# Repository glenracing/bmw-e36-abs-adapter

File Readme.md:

# bmw-e36-abs-adapter

BMW E36 ABS pedal travel sensor adapter and CANbus module.

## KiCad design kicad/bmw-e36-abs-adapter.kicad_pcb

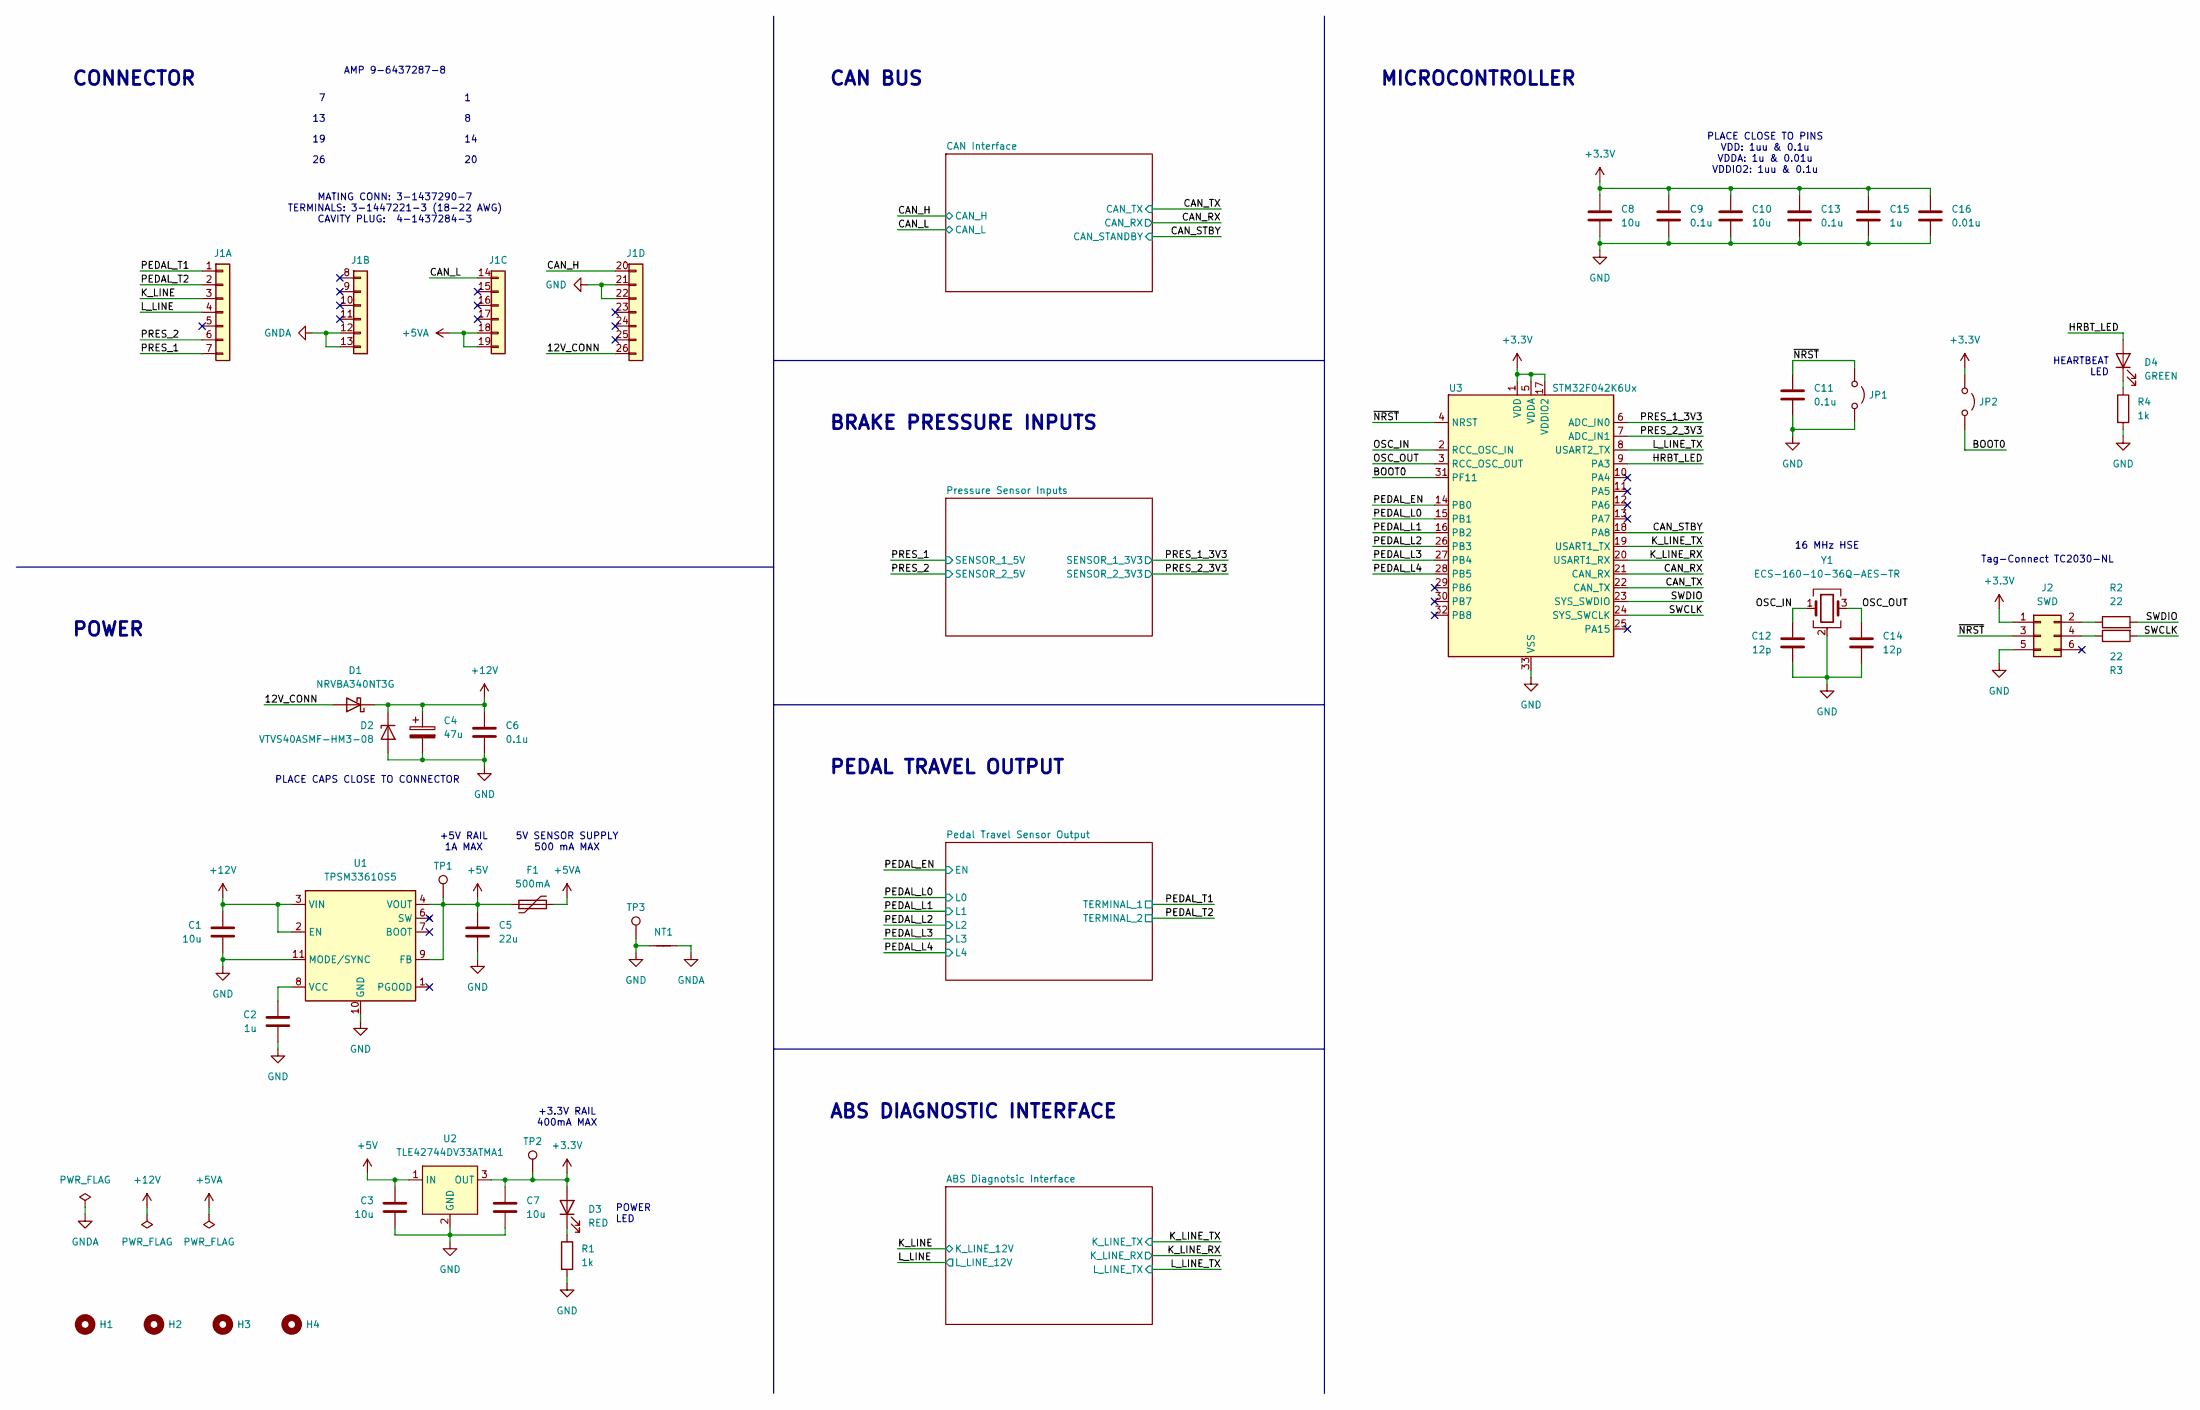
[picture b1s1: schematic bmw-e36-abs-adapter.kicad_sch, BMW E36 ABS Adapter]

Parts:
C1, C3, C7, C8, C10: 10u; C_1206_3216Metric; Part Number GRT31CR61H106KE01L
C2, C15: 1u; C_0603_1608Metric; Part Number GRT188R71E105KE13D
C4: 47u; CP_Elec_8x6.5; Part Number UCD1H470MCL6GS
C5: 22u; C_1206_3216Metric; Part Number GRT31CC81C226KE01L
C6, C9, C11, C13: 0.1u; C_0603_1608Metric; Part Number GCJ188R71H104KA12D
C12, C14: 12p; C_0603_1608Metric; Part Number GCM1885C2A120JA16D
C16: 0.01u; C_0603_1608Metric; Part Number GCM188R71H103KA37D
D1: NRVBA340NT3G; D_SMA; Part Number NRVBA340NT3G
D2: VTVS40ASMF-HM3-08; D_SMF; Part Number VTVS40ASMF-HM3-08
D3: RED; LED_0603_1608Metric; Part Number SML-D12V8WT86C
D4: GREEN; LED_0603_1608Metric; Part Number SML-D12P8WT86C
F1: 500mA; Fuse_1206_3216Metric; Part Number 0ZCJ0050AF2E
H1, H2, H3, H4: MountingHole; MountingHole_3.2mm_M3
J1: TE_9-6437287-8; Part Number 9-6437287-8
J2: SWD; Tag-Connect_TC2030-IDC-NL_2x03_P1.27mm_Vertical
JP1: RST; SolderJumper-2_P1.3mm_Open_RoundedPad1.0x1.5mm
JP2: BOOT; SolderJumper-2_P1.3mm_Open_RoundedPad1.0x1.5mm
NT1: NetTie_2; NetTie-2_SMD_Pad0.5mm
R1, R4: 1k; R_0603_1608Metric; Part Number ERJ-3EKF1001V
R2, R3: 22; R_0603_1608Metric; Part Number ERJ-3EKF22R0V
TP1, TP2: TestPoint; TestPoint_Pad_D1.5mm
TP3: TestPoint; TestPoint_Keystone_5000-5004_Miniature
U1: TPSM33610S5; Texas_RDN0011B_QFN-FCMOD-11-3.5x4.5mm-P0.5mm_2EP; Part Number TPSM33610S5QRDNRQ1
U2: TLE42744DV33ATMA1; TO-252-2; Part Number TLE42744DV33ATMA1
U3: STM32F042K6Ux; QFN-32-1EP_5x5mm_P0.5mm_EP3.45x3.45mm; Part Number STM32F042K6U6
Y1: ECS-160-10-36Q-AES-TR; Crystal_SMD_2520-4Pin_2.5x2.0mm; Part Number ECS-160-10-36Q-AES-TR

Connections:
+5VA: F1.2, J1.18, J1.19
+12V: C1.1, C4.1, C6.1, D1.1 (K), D2.1 (K), U1.2 (EN), U1.3 (VIN); also elsewhere on the board
/12V_CONN: D1.2 (A), J1.26
/BOOT0: JP2.2 (B), U3.31 (PF11)
/CAN_H: J1.20; also elsewhere on the board
/CAN_L: J1.14; also elsewhere on the board
/CAN_RX: U3.21 (CAN_RX); also elsewhere on the board
/CAN_STBY: U3.18 (PA8); also elsewhere on the board
/CAN_TX: U3.22 (CAN_TX); also elsewhere on the board
/HRBT_LED: D4.2 (A), U3.9 (PA3)
/K_LINE: J1.3; also elsewhere on the board
/K_LINE_RX: U3.20 (USART1_RX); also elsewhere on the board
/K_LINE_TX: U3.19 (USART1_TX); also elsewhere on the board
/L_LINE: J1.4; also elsewhere on the board
/L_LINE_TX: U3.8 (USART2_TX); also elsewhere on the board
/OSC_IN: C12.1, U3.2 (RCC_OSC_IN), Y1.1
/OSC_OUT: C14.1, U3.3 (RCC_OSC_OUT), Y1.3
/PEDAL_EN: U3.14 (PB0); also elsewhere on the board
/PEDAL_L0: U3.15 (PB1); also elsewhere on the board
/PEDAL_L1: U3.16 (PB2); also elsewhere on the board
/PEDAL_L2: U3.26 (PB3); also elsewhere on the board
/PEDAL_L3: U3.27 (PB4); also elsewhere on the board
/PEDAL_L4: U3.28 (PB5); also elsewhere on the board
/PEDAL_T1: J1.1; also elsewhere on the board
/PEDAL_T2: J1.2; also elsewhere on the board
/PRES_1: J1.7; also elsewhere on the board
/PRES_1_3V3: U3.6 (ADC_IN0); also elsewhere on the board
/PRES_2: J1.6; also elsewhere on the board
/PRES_2_3V3: U3.7 (ADC_IN1); also elsewhere on the board
/SWCLK: R3.2, U3.24 (SYS_SWCLK)
/SWDIO: R2.2, U3.23 (SYS_SWDIO)
/~NRST: C11.1, J2.3, JP1.1 (A), U3.4 (NRST)
GNDA: J1.12, J1.13, NT1.2; also elsewhere on the board
unnamed: D3.1 (K), R1.1
unnamed: D4.1 (K), R4.1
unnamed: J2.2, R2.1
unnamed: J2.4, R3.1
unnamed: C2.1, U1.8 (VCC)

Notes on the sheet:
16 MHz HSE
HEARTBEAT LED
PEDAL TRAVEL OUTPUT
AMP 9-6437287-8
Tag-Connect TC2030-NL
+5V RAIL 1A MAX
POWER LED
CONNECTOR
CAN BUS
PLACE CLOSE TO PINS VDD: 1uu & 0.1u VDDA: 1u & 0.01u VDDIO2: 1uu & 0.1u
MATING CONN: 3-1437290-7 TERMINALS: 3-1447221-3 (18-22 AWG) CAVITY PLUG: 4-1437284-3
MICROCONTROLLER
BRAKE PRESSURE INPUTS
+3.3V RAIL 400mA MAX
5V SENSOR SUPPLY 500 mA MAX
PLACE CAPS CLOSE TO CONNECTOR
ABS DIAGNOSTIC INTERFACE
POWER

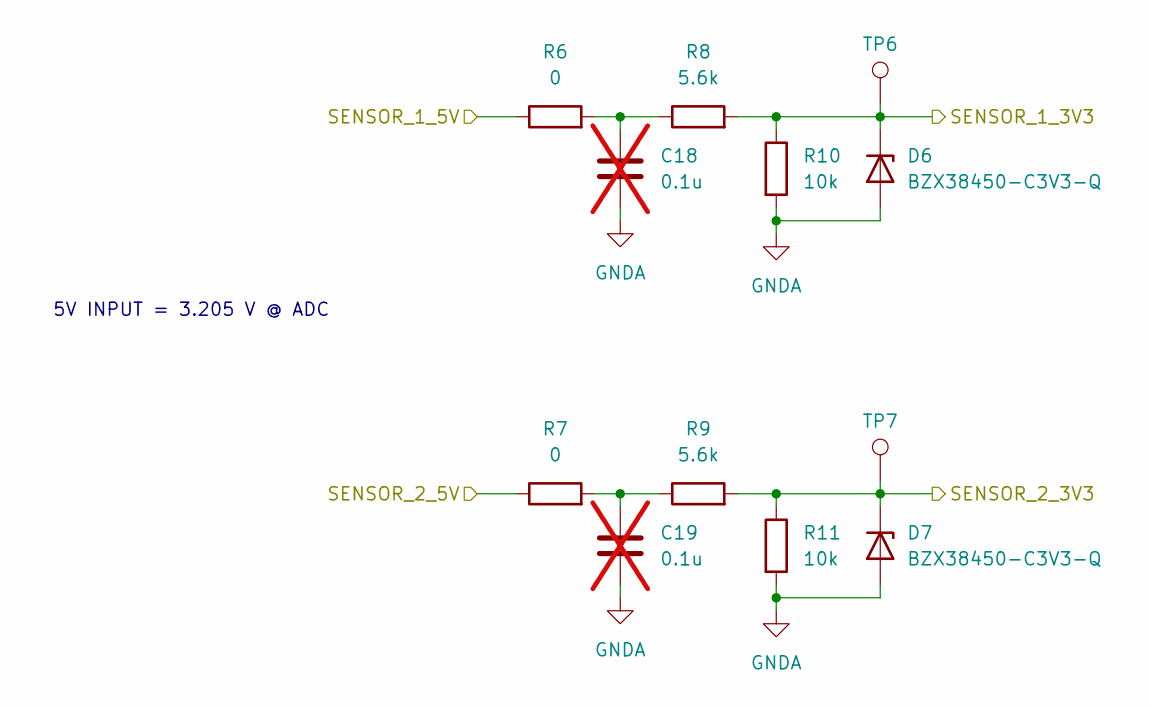
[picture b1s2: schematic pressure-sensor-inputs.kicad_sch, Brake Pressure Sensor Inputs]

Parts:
C18, C19: 0.1u; C_0603_1608Metric; Part Number GCJ188R71H104KA12D; not fitted
D6, D7: BZX38450-C3V3-Q; D_SOD-323; Part Number BZX38450-C3V3-Q
R6, R7: 0; R_0603_1608Metric; Part Number ERJ-H3G0R00V
R8, R9: 5.6k; R_0603_1608Metric; Part Number ERJ-3EKF5601V
R10, R11: 10k; R_0603_1608Metric; Part Number ERJ-3EKF1002V
TP6, TP7: TestPoint; TestPoint_Pad_D1.5mm

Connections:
/PRES_1: R6.1; also elsewhere on the board
/PRES_1_3V3: D6.1 (K), R8.2, R10.1, TP6.1 (1_1); also elsewhere on the board
/PRES_2: R7.1; also elsewhere on the board
/PRES_2_3V3: D7.1 (K), R9.2, R11.1, TP7.1 (1_1); also elsewhere on the board
GNDA: C18.2, C19.2, D6.2 (A), D7.2 (A), R10.2, R11.2; also elsewhere on the board
unnamed: C18.1, R6.2, R8.1
unnamed: C19.1, R7.2, R9.1

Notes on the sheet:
5V INPUT = 3.205 V @ ADC

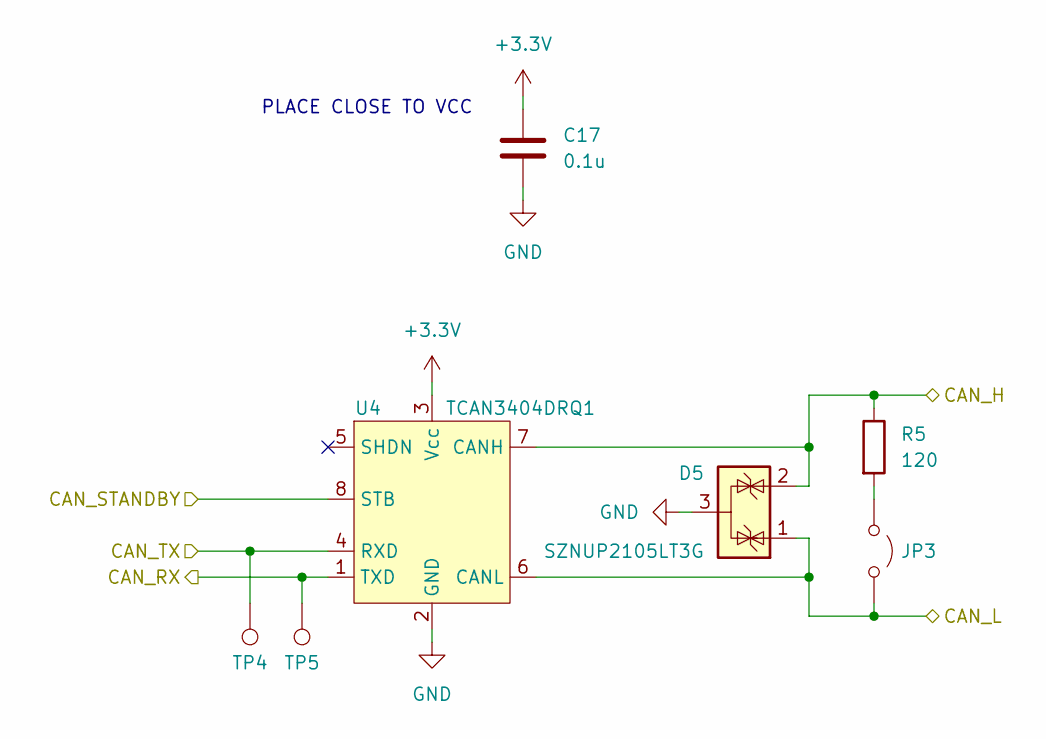
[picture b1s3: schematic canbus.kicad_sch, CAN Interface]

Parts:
C17: 0.1u; C_0603_1608Metric; Part Number GCJ188R71H104KA12D
D5: SZNUP2105LT3G; SOT-23; Part Number SZNUP2105LT3G
JP3: TERM; PinHeader_1x02_P2.54mm_Vertical; Part Number 61300211121
R5: 120; R_0603_1608Metric; Part Number ERJ-3EKF1200V
TP4, TP5: TestPoint; TestPoint_Pad_D1.5mm
U4: TCAN3404DRQ1; JEITA_SOIC-8_3.9x4.9mm_P1.27mm; Part Number TCAN3404DRQ1

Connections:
/CAN_H: D5.2 (K), R5.1, U4.7 (CANH); also elsewhere on the board
/CAN_L: D5.1 (K), JP3.2 (B), U4.6 (CANL); also elsewhere on the board
/CAN_RX: TP5.1 (1_1), U4.1 (TXD); also elsewhere on the board
/CAN_STBY: U4.8 (STB); also elsewhere on the board
/CAN_TX: TP4.1 (1_1), U4.4 (RXD); also elsewhere on the board
unnamed: JP3.1 (A), R5.2

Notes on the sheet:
PLACE CLOSE TO VCC

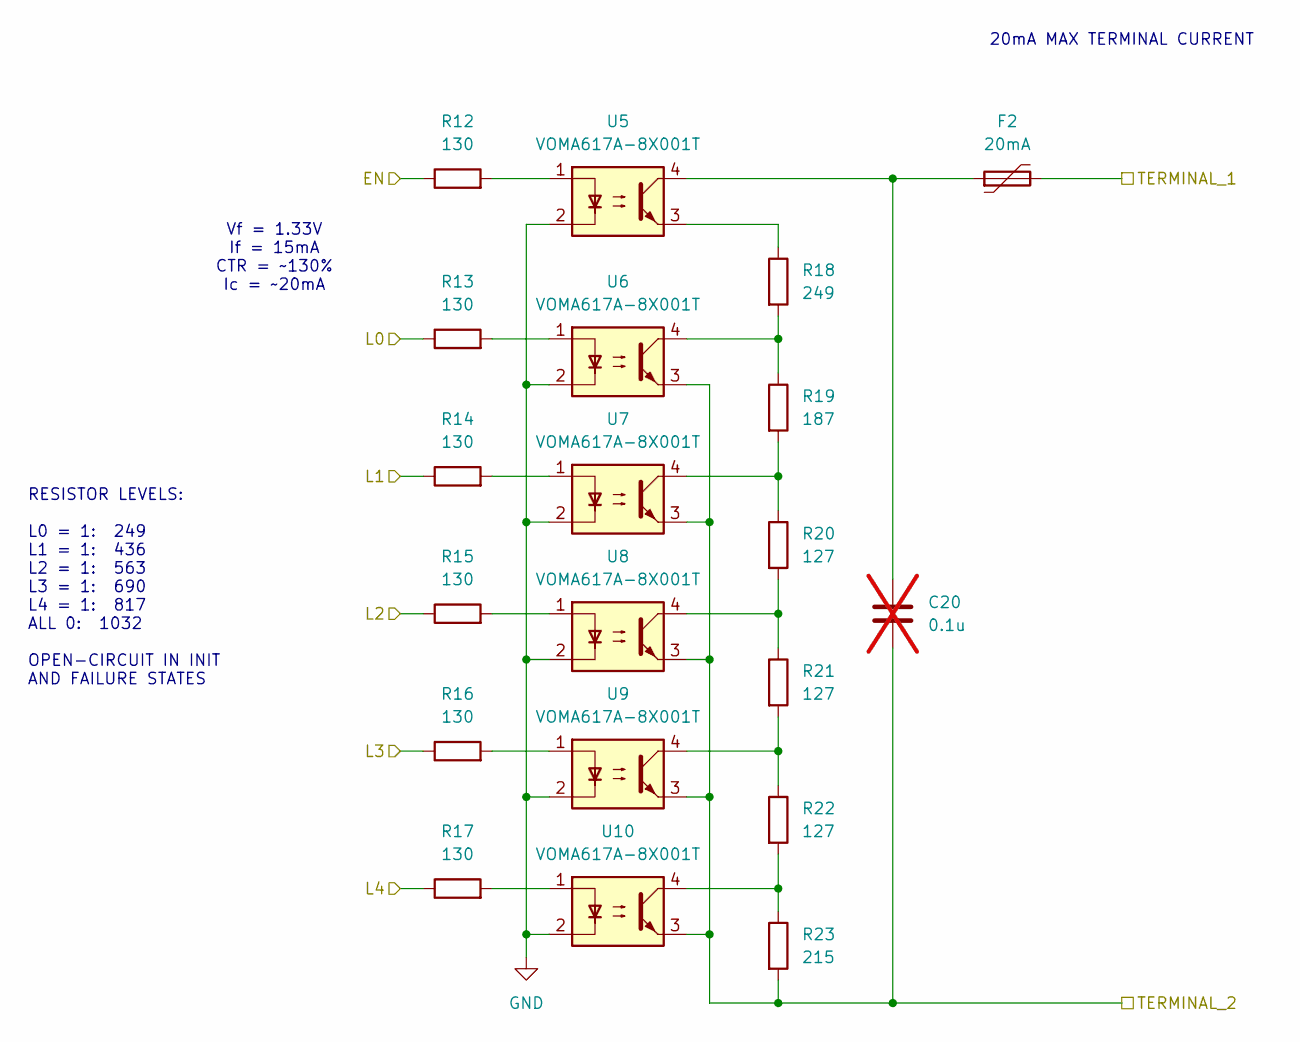
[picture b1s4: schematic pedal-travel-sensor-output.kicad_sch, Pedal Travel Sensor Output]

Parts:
C20: 0.1u; C_0603_1608Metric; Part Number GCJ188R71H104KA12D; not fitted
F2: 20mA; Fuse_0603_1608Metric; Part Number 0ZCM0002FF2G
R12, R13, R14, R15, R16, R17: 130; R_0603_1608Metric; Part Number ERJ-3EKF1300V
R18: 249; R_0603_1608Metric; Part Number ERJ-3EKF2490V
R19: 187; R_0603_1608Metric; Part Number ERJ-3EKF1870V
R20, R21, R22: 127; R_0603_1608Metric; Part Number ERJ-3EKF1270V
R23: 215; R_0603_1608Metric; Part Number ERJ-3EKF2150V
U5, U6, U7, U8, U9, U10: VOMA617A-8X001T; SOP-4_4.4x4.6mm_P2.54mm; Part Number VOMA617A-8X001T

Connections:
/PEDAL_EN: R12.1; also elsewhere on the board
/PEDAL_L0: R13.1; also elsewhere on the board
/PEDAL_L1: R14.1; also elsewhere on the board
/PEDAL_L2: R15.1; also elsewhere on the board
/PEDAL_L3: R16.1; also elsewhere on the board
/PEDAL_L4: R17.1; also elsewhere on the board
/PEDAL_T1: F2.2; also elsewhere on the board
/PEDAL_T2: C20.2, R23.2, U6.3, U7.3, U8.3, U9.3, U10.3; also elsewhere on the board
unnamed: C20.1, F2.1, U5.4
unnamed: R12.2, U5.1
unnamed: R13.2, U6.1
unnamed: R14.2, U7.1
unnamed: R15.2, U8.1
unnamed: R16.2, U9.1
unnamed: R17.2, U10.1
unnamed: R18.1, U5.3
unnamed: R18.2, R19.1, U6.4
unnamed: R19.2, R20.1, U7.4
unnamed: R20.2, R21.1, U8.4
unnamed: R21.2, R22.1, U9.4
unnamed: R22.2, R23.1, U10.4

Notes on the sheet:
20mA MAX TERMINAL CURRENT
Vf = 1.33V If = 15mA CTR = ~130% Ic = ~20mA
RESISTOR LEVELS: L0 = 1: 249 L1 = 1: 436 L2 = 1: 563 L3 = 1: 690 L4 = 1: 817 ALL 0: 1032 OPEN-CIRCUIT IN INIT AND FAILURE STATES

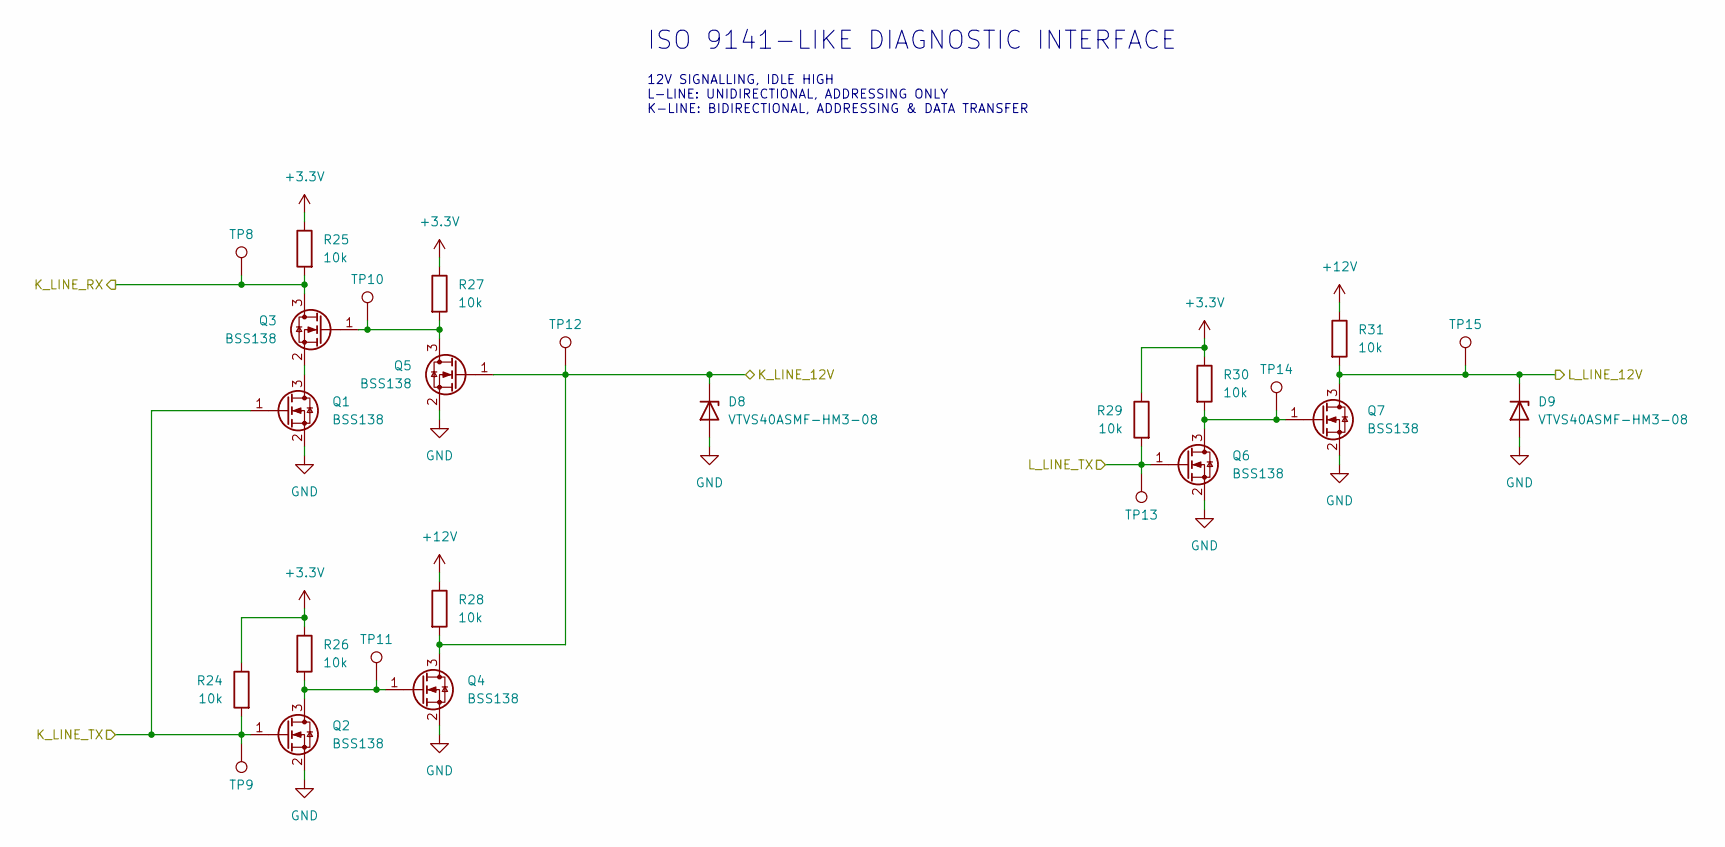
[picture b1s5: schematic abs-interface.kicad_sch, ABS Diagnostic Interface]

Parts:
D8, D9: VTVS40ASMF-HM3-08; D_SMF; Part Number VTVS40ASMF-HM3-08
Q1, Q2, Q3, Q4, Q5, Q6, Q7: BSS138; SOT-323_SC-70; Part Number BSS138PW,115
R24, R25, R26, R27, R28, R29, R30, R31: 10k; R_0603_1608Metric; Part Number ERJ-3EKF1002V
TP8, TP9, TP10, TP11, TP12, TP13, TP14, TP15: TestPoint; TestPoint_Pad_D1.5mm

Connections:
+12V: R28.1, R31.1; also elsewhere on the board
/K_LINE: D8.1 (K), Q4.3 (D), Q5.1 (G), R28.2, TP12.1 (1_1); also elsewhere on the board
/K_LINE_RX: Q3.3 (D), R25.2, TP8.1 (1_1); also elsewhere on the board
/K_LINE_TX: Q1.1 (G), Q2.1 (G), R24.2, TP9.1 (1_1); also elsewhere on the board
/L_LINE: D9.1 (K), Q7.3 (D), R31.2, TP15.1 (1_1); also elsewhere on the board
/L_LINE_TX: Q6.1 (G), R29.2, TP13.1 (1_1); also elsewhere on the board
unnamed: Q1.3 (D), Q3.2 (S)
unnamed: Q2.3 (D), Q4.1 (G), R26.2, TP11.1 (1_1)
unnamed: Q3.1 (G), Q5.3 (D), R27.2, TP10.1 (1_1)
unnamed: Q6.3 (D), Q7.1 (G), R30.2, TP14.1 (1_1)

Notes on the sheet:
ISO 9141-LIKE DIAGNOSTIC INTERFACE
12V SIGNALLING, IDLE HIGH L-LINE: UNIDIRECTIONAL, ADDRESSING ONLY K-LINE: BIDIRECTIONAL, ADDRESSING & DATA TRANSFER

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
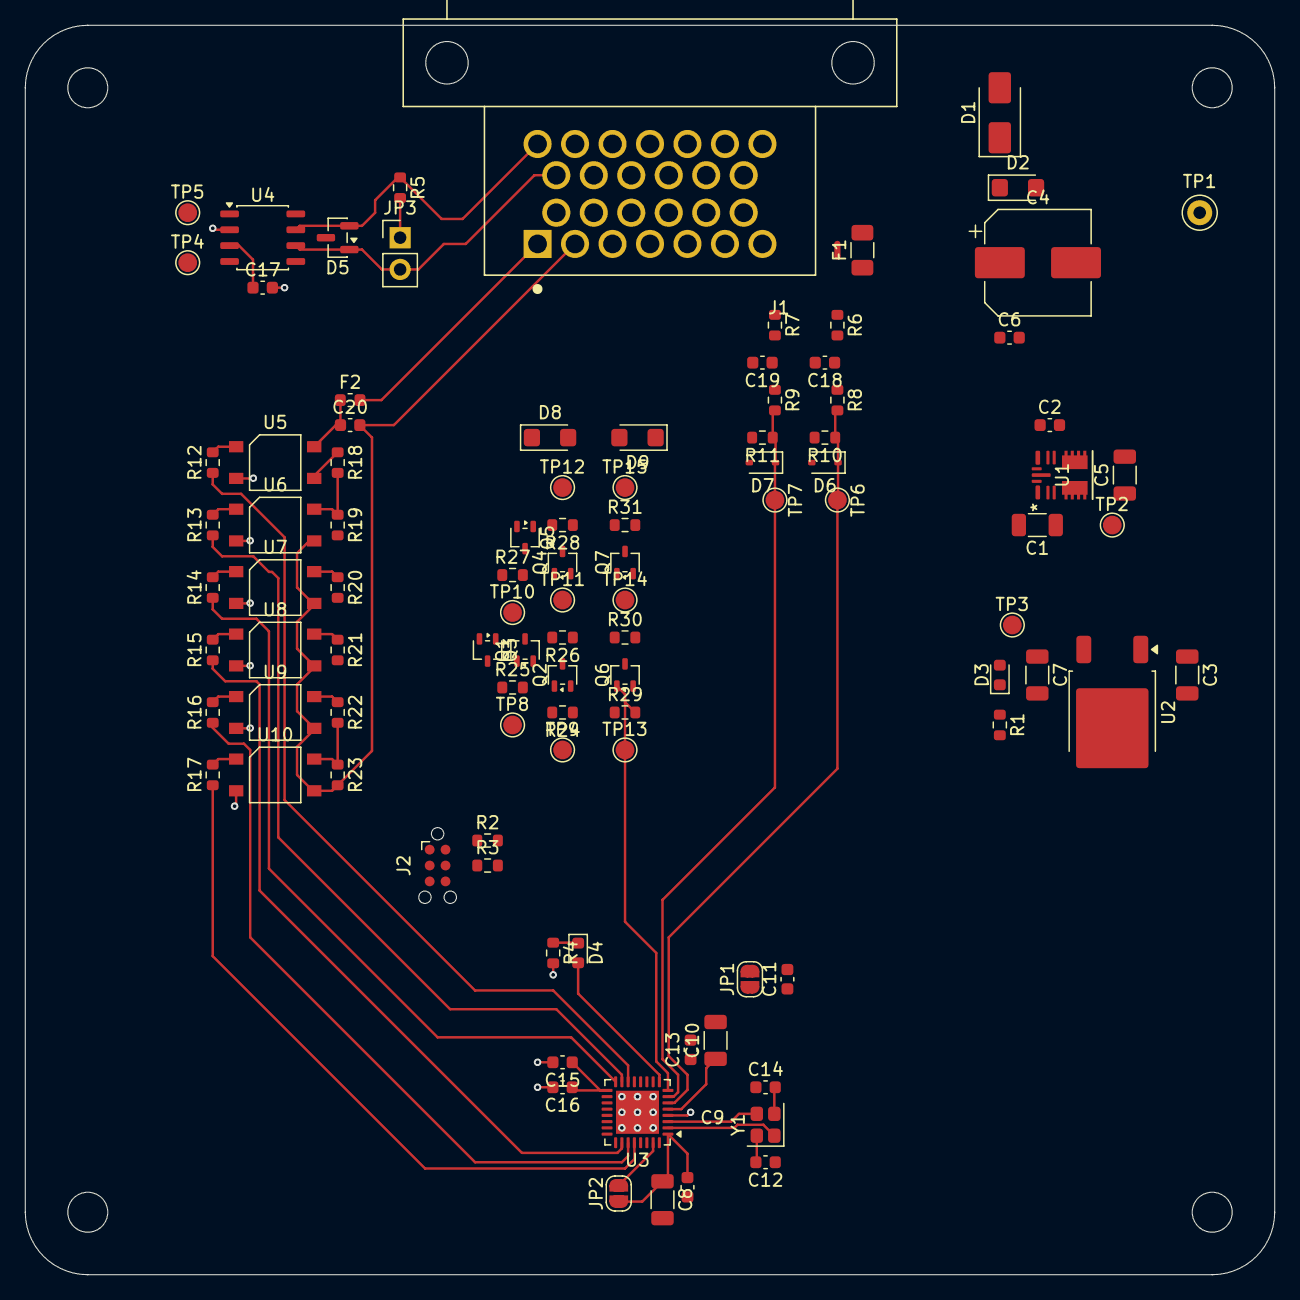
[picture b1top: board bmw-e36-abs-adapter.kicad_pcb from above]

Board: 2 copper layers, 100.0 x 100.0 mm, 105 parts (0 on the bottom side), 61 nets.

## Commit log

2026-04-06 Update gitignore
2026-04-06 Update power architecture and input protection
2026-04-06 Update canbus TVS protection
2026-04-06 Update ADC input divider and protection
2026-04-06 Update pedal travel output
2026-04-06 Update ABS diagnostic interface
2026-04-06 Update connector; annotate and assign footprints
2026-04-06 Add optional RC filter to pressure sensor inputs
2026-04-06 Add jumper for canbus termination
2026-04-06 Update footprints
2026-04-06 Update part numbers and fix ERC issues
2026-04-06 Export schematic and BOM
2026-04-07 BOM consolidation
2026-04-07 Use 3.3V LDO from ADC CAN module
2026-04-07 Update schematic and BOM
2026-04-07 Initial placement on PCB
2026-04-11 PCB Design WIP
